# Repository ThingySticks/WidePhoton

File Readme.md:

Wide Photon ThingyStick Prototype PCB
-------------------------------------

Wide format prototype board for Particle Photon.

Features:
=========

* USB power in via A Connector on left edge.
* Battery power in via JST under Photon. Do not use at the same time as power in via USB A or Photon USB.
* Pull-up or down 1206 pads on A0-A7. Suitable for 1206 or 0805 components.
* LED/Resistor/Capacitor 1206 pads along top edge, along both top and bottom or board (although you probably don't want both at once!)
* 4 mounting holes (M3 machine screw) to allow board to be mounted in case for final use.
* PCB 100mm x 40mm. Holes at 4mm from edge.

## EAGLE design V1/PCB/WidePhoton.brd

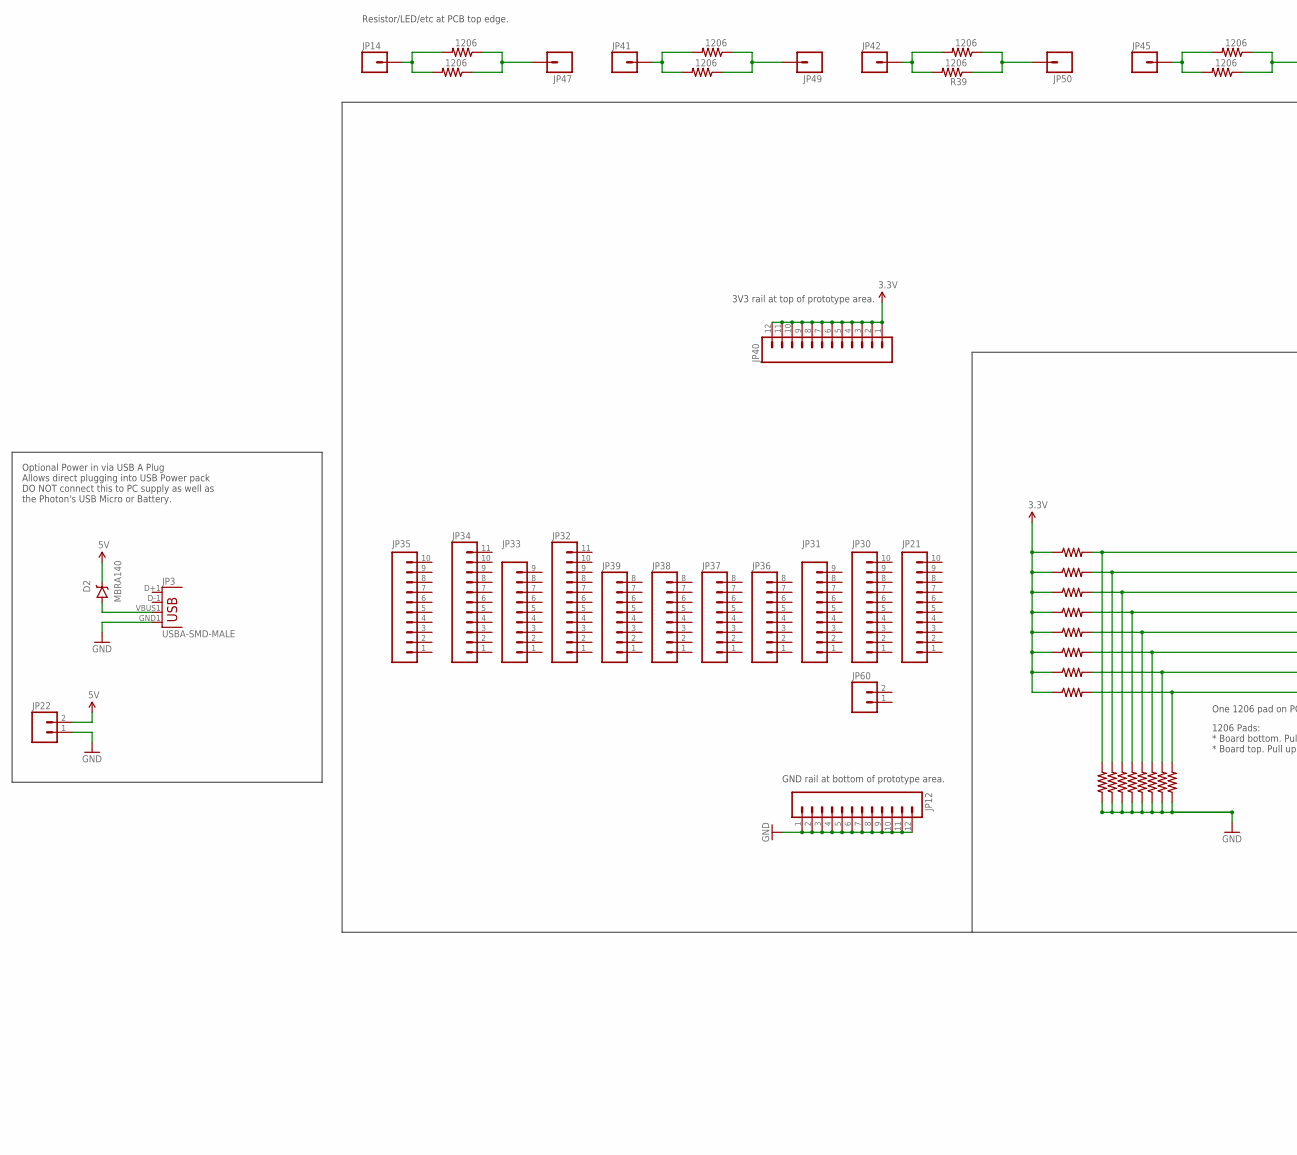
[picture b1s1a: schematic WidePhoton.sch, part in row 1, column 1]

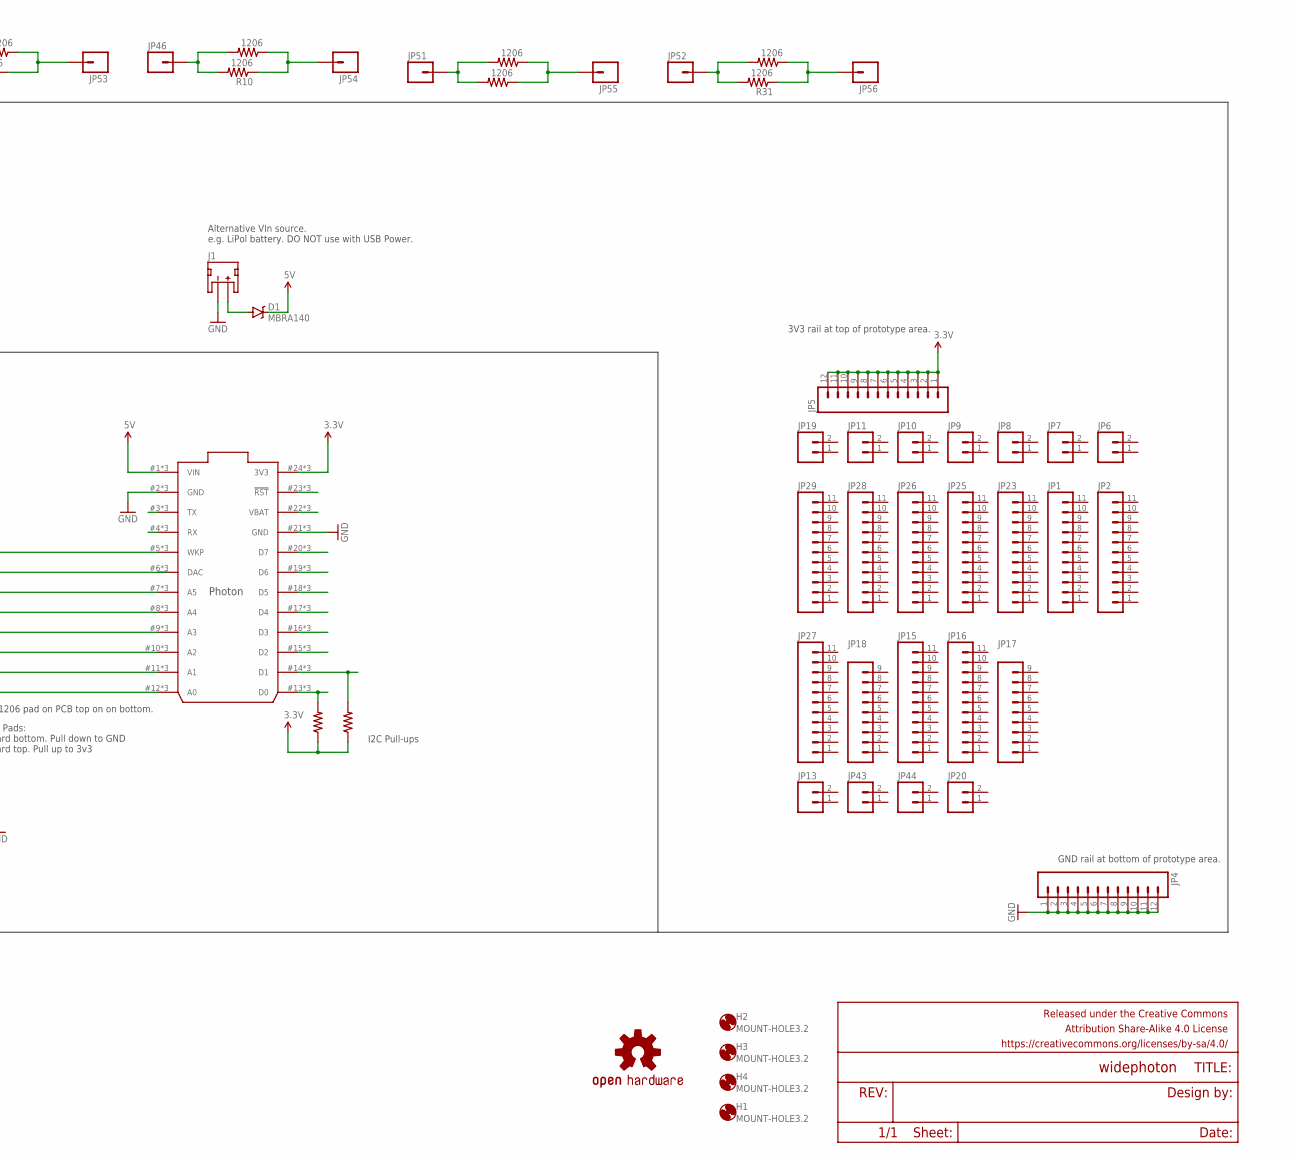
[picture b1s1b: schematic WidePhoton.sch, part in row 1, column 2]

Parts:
D1, D2: MBRA140; SMA-DIODE
FRAME1: FRAME-LEDGER; CREATIVE_COMMONS
H1, H2, H3, H4: MOUNT-HOLE3.2; 3,2
IC1: PHOTON_WITH_STACKABLE_HEADERS; PHOTON_STACKABLE
J1: JST_2MM_MALE; JST-2-SMD
JP1, JP2, JP15, JP16, JP23, JP25, JP26, JP27, JP28, JP29, JP32, JP34: M111X11_NO_SILK; 1X11_NO_SILK
JP3: USBA-SMD-MALE; USB-A-SMT-MALE
JP4, JP5, JP12, JP40: M12PTH; 1X12
JP6, JP7, JP8, JP9, JP10, JP11, JP13, JP19, JP20, JP22, JP43, JP44, JP60: M021X02_NO_SILK; 1X02_NO_SILK
JP14, JP41, JP42, JP45, JP46, JP47, JP49, JP50, JP51, JP52, JP53, JP54, JP55, JP56: M01PTH; 1X01
JP17, JP18, JP31, JP33: M09NO_SILK; 1X09_NO_SILK
JP21, JP30, JP35: M10NO_SILK_PTH_FEMALE; 1X10_NO_SILK
JP36, JP37, JP38, JP39: M08NO_SILK_FEMALE_PTH; 1X08_NO_SILK
LOGO1: OSHW-LOGOM; OSHW-LOGO-M
R1, R2, R3, R4, R5, R6, R7, R8, R9, R10, R12, R13, R14, R15, R16, R17, R19, R20, R21, R22, R24, R30, R31, R32, R34, R35, R36, R37, R39, R40, R41, R44: 1206

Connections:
3.3V: IC1.24 (3V3), IC1.#24 (3V3), IC1.@24 (3V3), JP5.1, JP5.2, JP5.3, JP5.4, JP5.5, JP5.6, JP5.7, JP5.8, JP5.9, JP5.10, JP5.11, JP5.12, JP40.1, JP40.2, JP40.3, JP40.4, JP40.5, JP40.6, JP40.7, JP40.8, JP40.9, JP40.10, JP40.11, JP40.12, R1.1, R2.1, R3.1, R4.1, R5.1, R6.1, R7.1, R9.1, R12.1, R15.1
5V: D1.C, D2.C, IC1.1 (VIN), IC1.#1 (VIN), IC1.@1 (VIN), JP22.2
GND: IC1.2 (GND), IC1.21 (GND), IC1.#2 (GND), IC1.#21 (GND), IC1.@2 (GND), IC1.@21 (GND), J1.1 (-), JP3.GND1 (GND), JP4.1, JP4.2, JP4.3, JP4.4, JP4.5, JP4.6, JP4.7, JP4.8, JP4.9, JP4.10, JP4.11, JP4.12, JP12.1, JP12.2, JP12.3, JP12.4, JP12.5, JP12.6, JP12.7, JP12.8, JP12.9, JP12.10, JP12.11, JP12.12, JP22.1, R8.1, R13.1, R14.1, R16.1, R19.1, R20.1, R21.1, R22.1
unnamed: JP42.1, R39.2, R44.2
unnamed: IC1.22 (VBAT), IC1.#22 (VBAT), IC1.@22 (VBAT)
unnamed: IC1.20 (D7), IC1.#20 (D7), IC1.@20 (D7)
unnamed: JP53.1, R17.1, R24.1
unnamed: JP45.1, R17.2, R24.2
unnamed: IC1.5 (WKP), IC1.#5 (WKP), IC1.@5 (WKP), R8.2, R12.2
unnamed: IC1.6 (DAC), IC1.#6 (DAC), IC1.@6 (DAC), R15.2, R16.2
unnamed: IC1.7 (A5), IC1.#7 (A5), IC1.@7 (A5), R1.2, R13.2
unnamed: IC1.8 (A4), IC1.#8 (A4), IC1.@8 (A4), R2.2, R14.2
unnamed: IC1.9 (A3), IC1.#9 (A3), IC1.@9 (A3), R3.2, R19.2
unnamed: IC1.10 (A2), IC1.#10 (A2), IC1.@10 (A2), R4.2, R20.2
unnamed: IC1.11 (A1), IC1.#11 (A1), IC1.@11 (A1), R6.2, R21.2
unnamed: IC1.12 (A0), IC1.#12 (A0), IC1.@12 (A0), R7.2, R22.2
unnamed: IC1.19 (D6), IC1.#19 (D6), IC1.@19 (D6)
unnamed: IC1.13 (D0), IC1.#13 (D0), IC1.@13 (D0), R5.2
unnamed: IC1.14 (D1), IC1.#14 (D1), IC1.@14 (D1), R9.2
unnamed: IC1.18 (D5), IC1.#18 (D5), IC1.@18 (D5)
unnamed: IC1.17 (D4), IC1.#17 (D4), IC1.@17 (D4)
unnamed: IC1.16 (D3), IC1.#16 (D3), IC1.@16 (D3)
unnamed: IC1.15 (D2), IC1.#15 (D2), IC1.@15 (D2)
unnamed: JP46.1, R10.2, R30.2
unnamed: JP54.1, R10.1, R30.1
unnamed: JP55.1, R32.1, R36.1
unnamed: JP51.1, R32.2, R36.2
unnamed: JP56.1, R31.1, R37.1
unnamed: JP52.1, R31.2, R37.2
unnamed: IC1.4 (RX), IC1.#4 (RX), IC1.@4 (RX)
unnamed: IC1.3 (TX), IC1.#3 (TX), IC1.@3 (TX)
unnamed: D2.A, JP3.VBUS1 (VBUS)
unnamed: IC1.23 (!RST), IC1.#23 (!RST), IC1.@23 (!RST)
unnamed: D1.A, J1.2 (+)
unnamed: JP47.1, R34.1, R35.1
unnamed: JP14.1, R34.2, R35.2
unnamed: JP49.1, R40.1, R41.1
unnamed: JP41.1, R40.2, R41.2
unnamed: JP50.1, R39.1, R44.1

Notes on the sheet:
Resistor/LED/etc at PCB top edge.
Optional Power in via USB A Plug Allows direct plugging into USB Power pack DO NOT connect this to PC supply as well as the Photon's USB Micro or Battery.
GND rail at bottom of prototype area.
3V3 rail at top of prototype area.
One 1206 pad on PCB top on on bottom.
1206 Pads: * Board bottom. Pull down to GND * Board top. Pull up to 3v3
Alternative VIn source. e.g. LiPol battery. DO NOT use with USB Power.
I2C Pull-ups

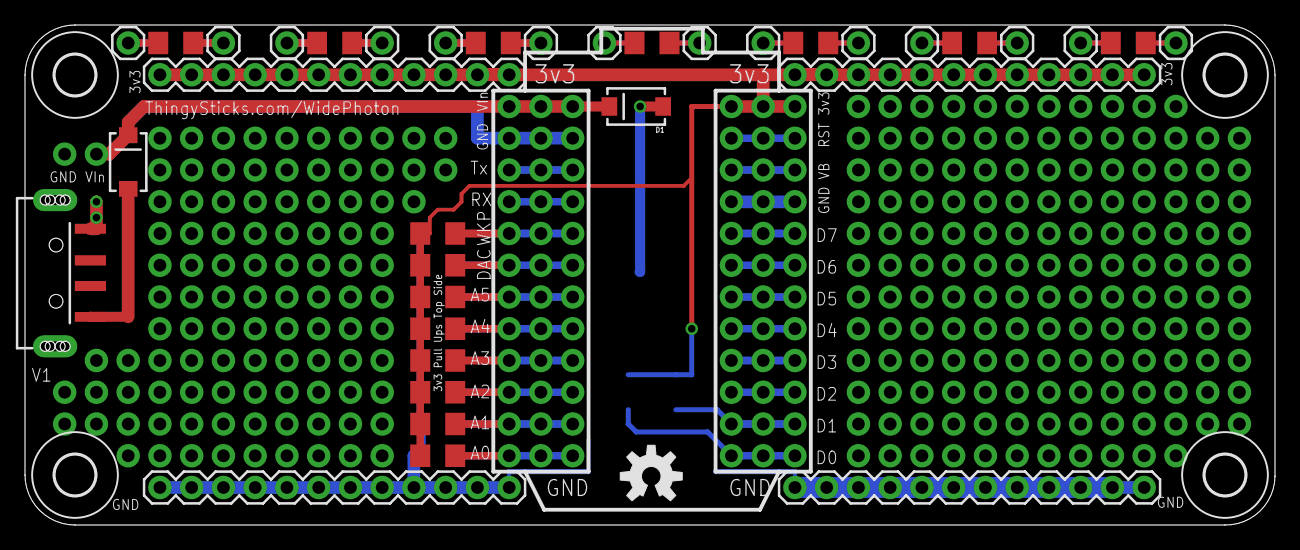
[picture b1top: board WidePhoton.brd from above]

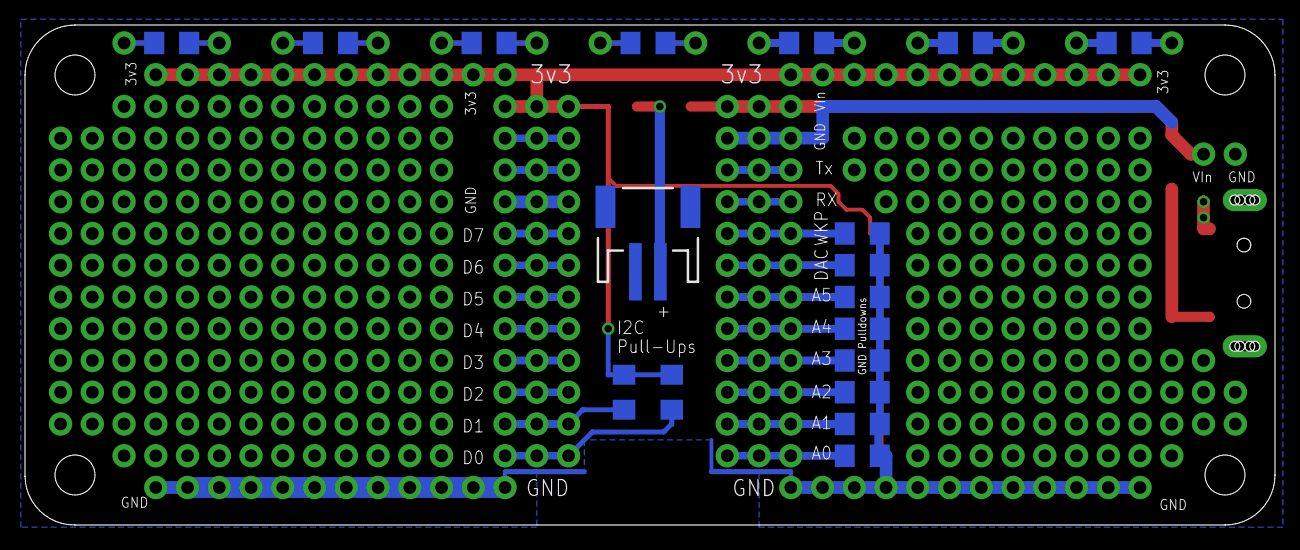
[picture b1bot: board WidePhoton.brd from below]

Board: 2 copper layers, 100.0 x 40.0 mm, 97 parts (18 on the bottom side), 39 nets.

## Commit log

2016-11-18 Moved from Thing On A Stick repository. Removed D0-D7 pull-up/down resistors. Metricified outline and hole positions. Changed mounting holes to 3.2mm for better fit with M3 machine srew. Improved sil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
2016-11-18 Renamed files to WidePhoton Added OSH logo. Improved reverse power labels. Added diodes for battery/USB A protection. Added gitignore.
2016-11-18 Added pdfs
2016-11-20 DirtyPCB Images.
2017-01-04 Added BOM.
2017-01-04 Fixed json validation issues for BOM.

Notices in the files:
parts and their libraries:
SparkFun-Connectors: Licensing: Creative Commons ShareAlike 4.0 International - https://creativecommons.org/licenses/by-sa/4.0
SparkFun-Aesthetics: Released under the Creative Commons Attribution Share-Alike 4.0 License
SparkFun-Aesthetics: https://creativecommons.org/licenses/by-sa/4.0
